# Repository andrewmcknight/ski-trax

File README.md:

# Ski-Trax

Ski-Trax is an embedded tracking node built around the Heltec WiFi LoRa 32 V3. The goal is a rugged device that skiers can use to find their friends/family on the slopes, without needing a phone with cell service.

## Hardware Stack
- **Main MCU:** Heltec WiFi LoRa 32 V3 (ESP32-S3 + SX1262)
- **GNSS:** SparkFun MAX-M10S breakout (I2C)
- **Display:** Adafruit 2.2" TFT (ILI9341 driver) connected through the Adafruit EYESPI breakout (SPI)
- **IMU:** Adafruit BNO055 9-DOF sensor (I2C)
- **Barometer:** Adafruit BMP390 (I2C)
- **Inputs/Outputs:** Three external buttons, piezo buzzer, TFT backlight PWM

## Pin Assignments
| Function | Heltec GPIO | Notes |
|----------|-------------|-------|
| I2C SDA | 47 | Shared by MAX-M10S, BNO055, BMP390 |
| I2C SCL | 48 | Shared by MAX-M10S, BNO055, BMP390 |
| TFT SCK | 3 | Hardware SPI via EyeSPI ribbon |
| TFT MOSI | 4 | Hardware SPI via EyeSPI ribbon |
| TFT CS | 7 | |
| TFT D/C | 5 | |
| TFT RST | 6 | |
| TFT Backlight PWM | 2 | Driven with LEDC PWM |
| Button – Dim | 40 | Input with pull-up |
| Button – Buzzer | 41 | Input with pull-up |
| Button – Brighten | 42 | Input with pull-up |
| Piezo Buzzer | 39 | LEDC PWM output |

> Note: LoRa radio is built into the Heltec board.

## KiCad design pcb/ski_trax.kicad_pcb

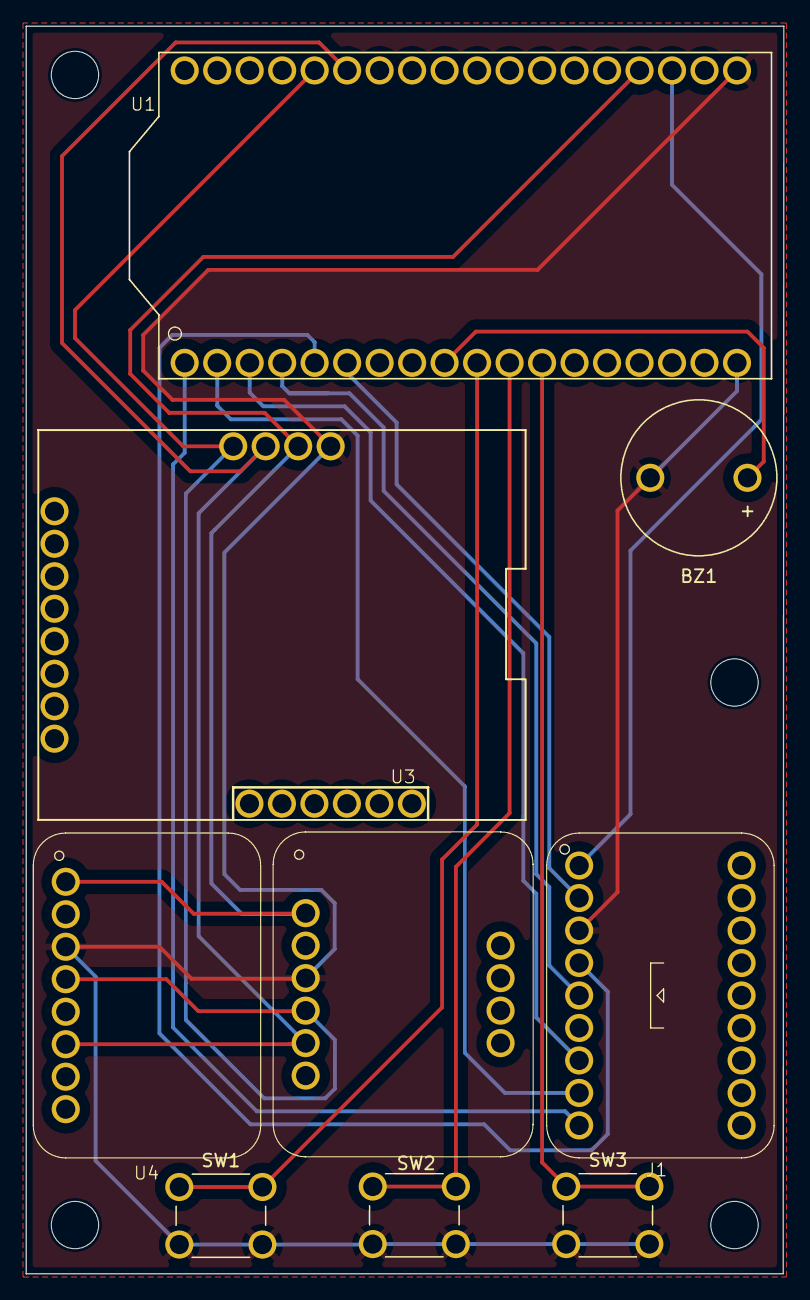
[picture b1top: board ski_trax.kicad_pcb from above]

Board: 2 copper layers, 59.2 x 97.5 mm, 9 parts (0 on the bottom side), 15 nets.

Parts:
BZ1: Buzzer; Buzzer_12x9.5RM7.6
J1: Adafruit_EYESPI_Breakout
SW1, SW2, SW3: SW_Push; SW_PUSH_6mm
U1: Heltec_WiFi_LoRa_32_v3
U2: sparkfun_max_m10s_breakout
U3: Adafruit_BNO055
U4: Adafruit_BMP390

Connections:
3V3_1: U1.22 (Ve), U2.16 (3V3), U3.1 (VIN), U4.1 (VIN)
3V3_2: J1.1 (VIN), U1.21 (Ve)
BUZ: BZ1.1 (+), U1.9 (39)
GND: BZ1.2 (-), J1.3 (Gnd), SW1.1, SW2.1, SW3.1, U1.18 (GND), U1.19 (GND), U2.15 (GND), U3.3 (GND), U4.3 (GND)
SCL: U1.32 (48), U2.18 (SCL), U3.4 (SCL), U4.4 (SCL)
SDA: U1.31 (47), U2.17 (SDA), U3.5 (SDA), U4.6 (SDA)
SW1: SW1.2, U1.10 (40)
SW2: SW2.2, U1.11 (41)
SW3: SW3.2, U1.12 (42)
TFT_CLK: J1.4 (SCK), U1.5 (3)
TFT_DC: J1.7 (DC), U1.3 (5)
TFT_LCDCS: J1.9 (TCS), U1.1 (7)
TFT_LITE: J1.2 (Lite), U1.6 (2)
TFT_MOSI: J1.5 (MOSI), U1.4
TFT_RST: J1.8 (RST), U1.2 (6)

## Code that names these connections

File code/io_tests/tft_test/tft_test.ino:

/*
 * ILI9341 Display Test for EyeSPI Breakout (Heltec WiFi LoRa 32 V3)
 * -----------------------------------------------------------------
 * Core TFT pin mapping (EyeSPI -> Heltec):
 *   - VCC  -> 3V3
 *   - GND  -> GND
 *   - SCK  -> GPIO3
 *   - MOSI -> GPIO4
 *   - CS   -> GPIO7
 *   - D/C  -> GPIO5
 *   - RST  -> GPIO6
 *   - MISO -> not connected
 */

// **Working as of 11/11/25**

#include <Adafruit_GFX.h>
#include <Adafruit_ILI9341.h>
#include <SPI.h>

// EyeSPI -> Heltec WiFi LoRa 32 V3 pin assignments
#define TFT_CS   7
#define TFT_RST  6
#define TFT_DC   5
#define TFT_MOSI 4
#define TFT_SCK  3
#define TFT_MISO -1  // Not used (write-only TFT)

#define VEXT_CTRL 36

// Safe SPI clock (ILI9341 supports up to 40 MHz)
#define TFT_SPI_FREQUENCY  20000000UL

SPIClass tftSpi(HSPI);  // Dedicated HSPI bus so we don't disturb the SX1262 SPI wiring
Adafruit_ILI9341 tft(&tftSpi, TFT_DC, TFT_CS, TFT_RST);

static void configureSpiPins() {
  tftSpi.begin(TFT_SCK, TFT_MISO, TFT_MOSI, TFT_CS);
}

static void runScreenTest() {
  tft.fillScreen(ILI9341_BLACK);
  delay(250);
  tft.fillScreen(ILI9341_RED);
  delay(250);
  tft.fillScreen(ILI9341_GREEN);
  delay(250);
  tft.fillScreen(ILI9341_BLUE);
  delay(250);
  tft.fillScreen(ILI9341_BLACK);

  tft.drawRect(0, 0, tft.width(), tft.height(), ILI9341_WHITE);
  tft.setTextSize(2);
  tft.setTextColor(ILI9341_YELLOW, ILI9341_BLACK);
  tft.setCursor(8, 8);
  tft.print("EyeSPI TFT Test");

  tft.setTextSize(1);
  tft.setCursor(8, 32);
  tft.setTextColor(ILI9341_CYAN, ILI9341_BLACK);
  tft.print("CS="), tft.print(TFT_CS);
  tft.print("  DC="), tft.print(TFT_DC);
  tft.print("  RST="), tft.print(TFT_RST);

  tft.setCursor(8, 48);
  tft.print("MOSI="), tft.print(TFT_MOSI);
  tft.print("  SCK="), tft.print(TFT_SCK);

  tft.drawLine(0, 0, tft.width(), tft.height(), ILI9341_MAGENTA);
  tft.drawLine(0, tft.height(), tft.width(), 0, ILI9341_MAGENTA);
}

void setup() {
  Serial.begin(115200);
  delay(200);

  // === ENABLE VEXT POWER RAIL ===
  pinMode(VEXT_CTRL, OUTPUT);
  digitalWrite(VEXT_CTRL, LOW);   // Turn on Vext 3.3V output
  delay(50); // give sensors time to power up
  // ===============================

  Serial.println("\n=== EyeSPI ILI9341 Test (Core TFT Pins) ===");
  Serial.printf("CS=%d  DC=%d  RST=%d  MOSI=%d  SCK=%d\n",
                TFT_CS, TFT_DC, TFT_RST, TFT_MOSI, TFT_SCK);

  configureSpiPins();

  Serial.println("Initialising display...");
  tft.begin(TFT_SPI_FREQUENCY);
  tft.setRotation(1);
  runScreenTest();
  Serial.println("Display initialised!");
}

void loop() {
  static uint32_t lastBlink = 0;
  static bool on = false;

  if (millis() - lastBlink > 500) {
    lastBlink = millis();
    on = !on;
    tft.drawPixel(4, 4, on ? ILI9341_GREEN : ILI9341_BLACK);
    Serial.print(on ? "*" : ".");
  }
}

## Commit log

2025-10-23 GPS and LoRa working
2025-11-03 Update repo
2025-11-10 Update repo structure
2025-11-10 Add missing files
2025-11-11 Add full-stack I/O validation sketches
2025-11-11 Change TFT connectivity to EYESPI
2025-11-11 Add EyeSPI-specific TFT diagnostic sketch
2025-11-11 Update documentation
2025-11-11 Update EyeSPI TFT pin map for Heltec WiFi LoRa 32 V3
2025-11-11 Fix tft test
2025-11-11 Update full stack test controls and layout
2025-11-11 Draft project overview README
2025-11-13 Add PCB files
2025-11-16 Update PCB files
2025-11-18 CompassPics
2025-11-19 NewNewCompass
2025-11-19 Organize compass files
2025-11-19 Start firmware skeleton
2025-11-19 Clean up repo structure
2025-11-19 Fix folder mistake
2025-11-19 NeedlePics
2025-11-19 (LOWER RES)
2025-11-20 SatImage
2025-11-20 Full UI Rendering
2025-11-21 Update code
2025-11-21 Fix compass needle
2025-11-21 Fixed joey and molly tracking
2025-11-21 Add images
